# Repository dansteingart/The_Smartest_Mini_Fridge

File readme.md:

##Updated With Code from Class 2019

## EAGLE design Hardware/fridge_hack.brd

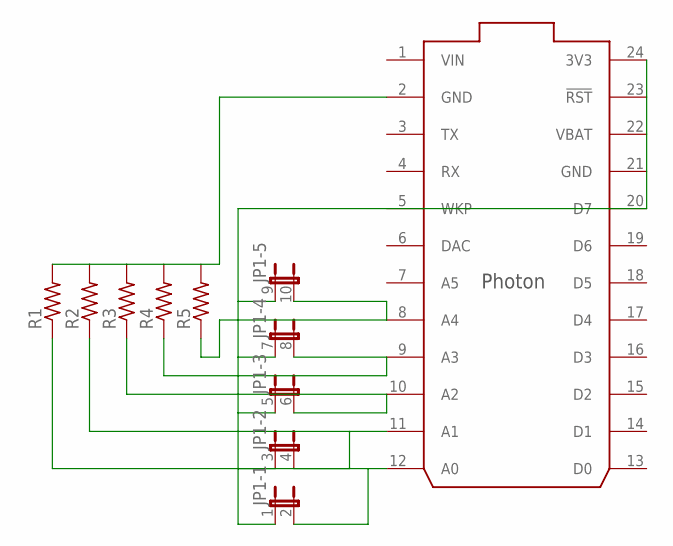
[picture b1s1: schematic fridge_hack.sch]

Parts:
JP1: JP5QE; JP5Q
R1, R2, R3, R4, R5: R-US_0309/12; 0309/12
U$1: PHOTON_WITH_HEADERS; PHOTON

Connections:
GND: U$1.21 (GND)
unnamed: R1.2, R2.2, R3.2, R4.2, R5.2, U$1.2 (GND)
unnamed: JP1.1, JP1.3 (1), JP1.5 (1), JP1.7 (1), JP1.9 (1), U$1.24 (3V3)
unnamed: JP1.10 (2), R5.1, U$1.8 (A4)
unnamed: JP1.8 (2), R4.1, U$1.9 (A3)
unnamed: JP1.6 (2), R3.1, U$1.10 (A2)
unnamed: JP1.4 (2), R2.1, U$1.11 (A1)
unnamed: JP1.2, R1.1, U$1.12 (A0)
VBAT: U$1.22 (VBAT)
VIN: U$1.1 (VIN)

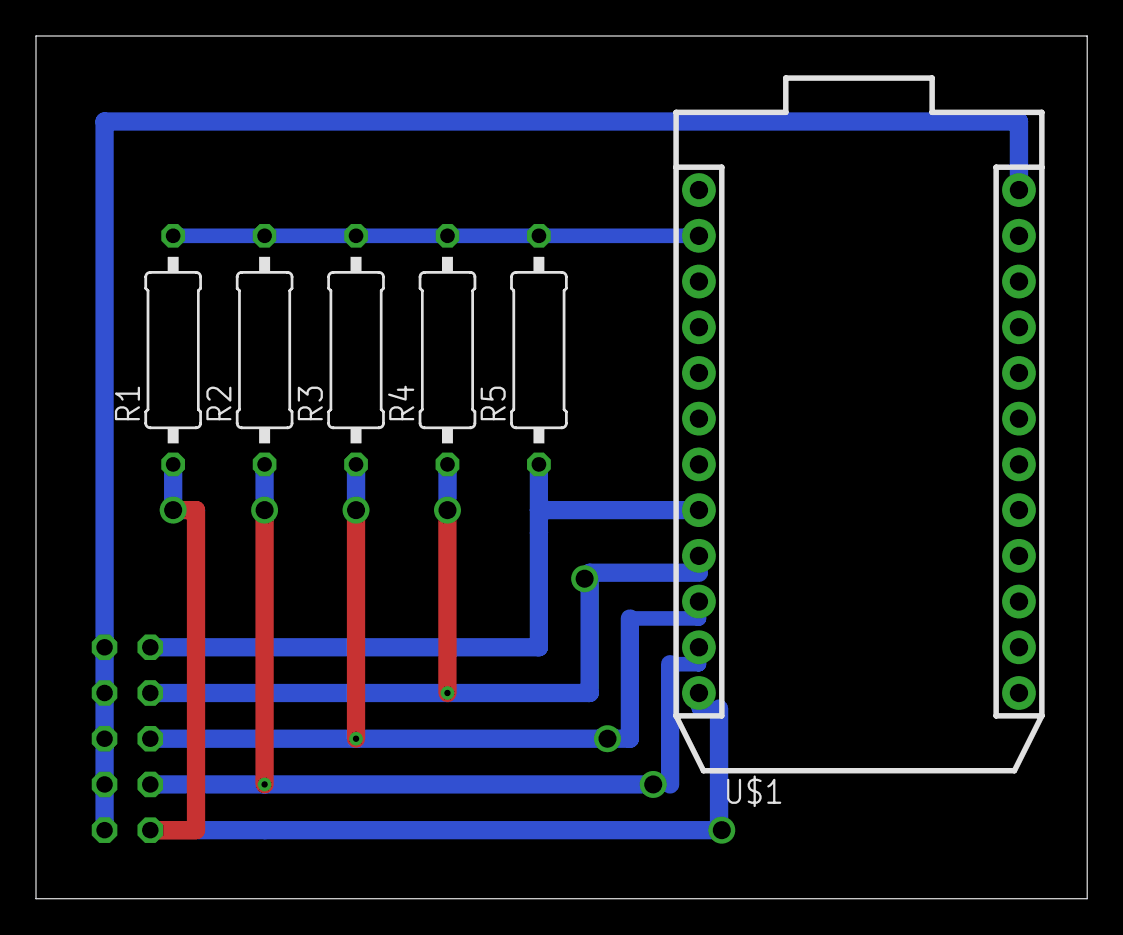
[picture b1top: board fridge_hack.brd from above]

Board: 2 copper layers, 58.4 x 47.9 mm, 7 parts (1 on the bottom side), 7 nets.

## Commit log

2018-07-31 firmware push
2018-07-31 stages
2018-07-31 remove test
2018-08-01 PID working for heat
2018-08-02 lots of changes
2018-08-02 more changes
2018-08-02 adding display libraries
2018-08-17 switch thermistor

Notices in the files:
parts and their libraries:
Particle-Devices: Licensing: Designed by Particle.
